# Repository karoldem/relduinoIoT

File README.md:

# relduinoIoT
KiCAD project of Arduinoish board with relay and ESP-01 on it.

Disclaimer - I hereby reject any responsibility for usage of this device. Seriously, guys, don't plug any random schematic form Internet to the grid without being trained electrician.

On board:
  ESP-01
  4 relays
  6 channel ADC
  2 PWM channels
  LEDS and microswitches
  
Not on a board:
  5V 1A power supply (I will use obsolete phone charger, that comes dime a dozen)

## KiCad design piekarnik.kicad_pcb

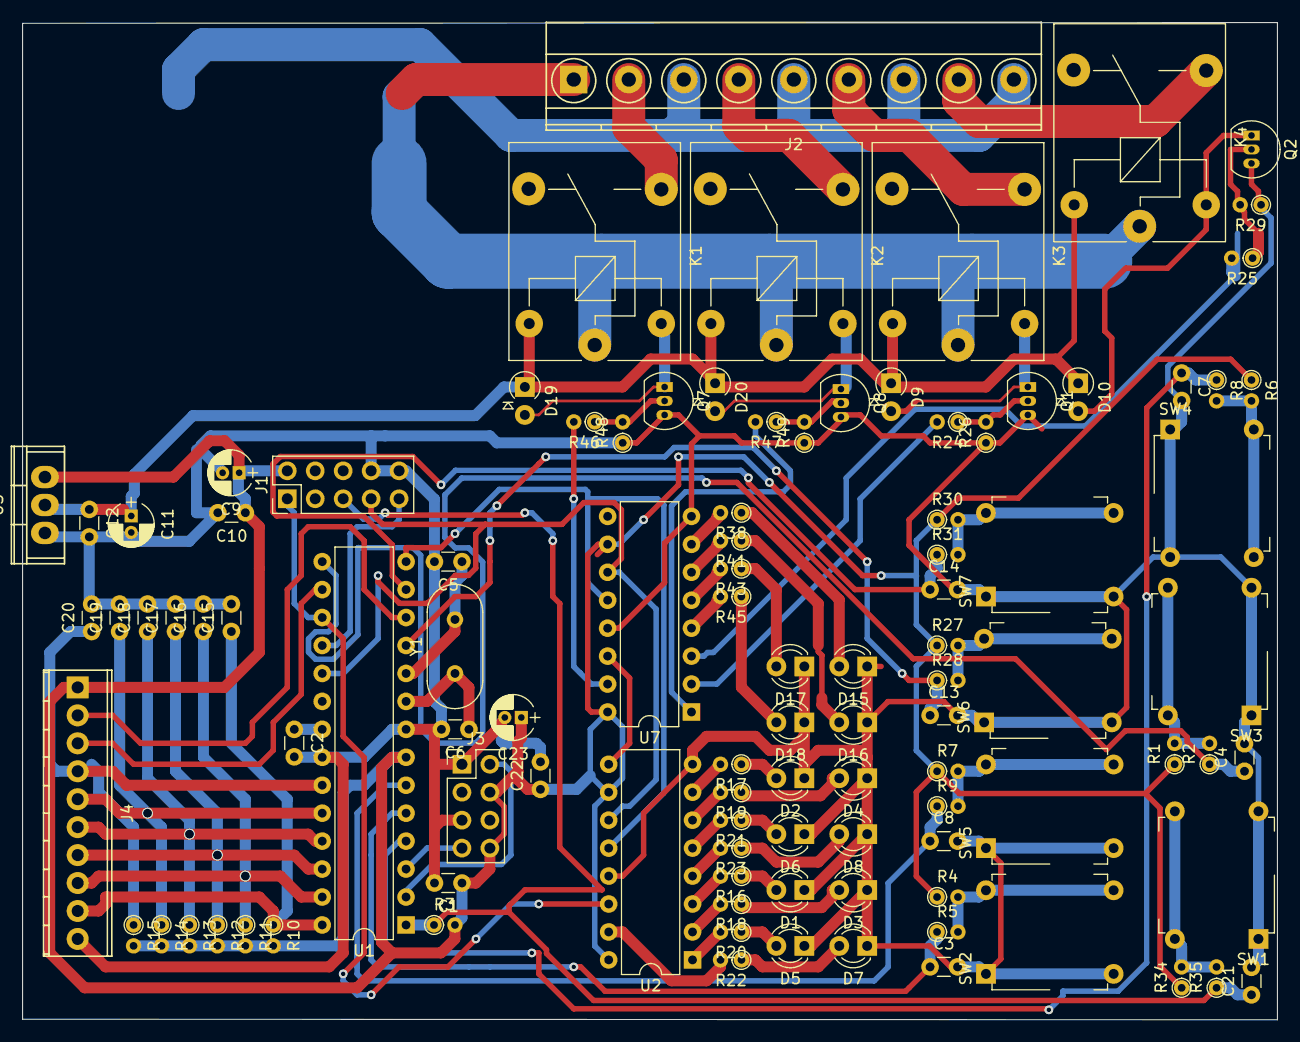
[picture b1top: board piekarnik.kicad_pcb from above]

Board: 2 copper layers, 114.1 x 90.6 mm, 104 parts (0 on the bottom side), 77 nets.

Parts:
C1, C2, C10, C12, C15, C16, C17, C18, C19, C20, C22: 100n; C_Disc_D3.0mm_W1.6mm_P2.50mm
C3, C4, C7, C8, C13, C14, C21: 10u; C_Disc_D3.0mm_W1.6mm_P2.50mm
C5, C6: 22p; C_Disc_D3.0mm_W1.6mm_P2.50mm
C9, C11, C23: 22u; CP_Radial_D4.0mm_P1.50mm
D1, D2, D3, D4, D5, D6, D7, D8, D15, D16, D17, D18: LED; LED_D3.0mm
D9, D10, D19, D20: D; D_A-405_P2.54mm_Vertical_AnodeUp
J1: Conn_02x05_Odd_Even; PinHeader_2x05_P2.54mm_Vertical
J2: Screw_Terminal_01x09; TerminalBlock_Phoenix_MKDS1.5-9pol
J3: Conn_02x04_Odd_Even; PinHeader_2x04_P2.54mm_Vertical
J4: Screw_Terminal_01x10; TerminalBlock_Phoenix_MPT-2.54mm_10pol
K1, K2, K3, K4: SANYOU_SRD_Form_C; Relay_SPDT_SANYOU_SRD_Series_Form_C
Q1, Q2, Q7, Q8: BC237; TO-92_Inline_Narrow_Oval
R1, R2, R3, R4, R5, R6, R7, R8, R9, R10, R11, R12, R13, R14, R15, R27, R28, R30, R31, R34, R35: 10k; R_Axial_DIN0204_L3.6mm_D1.6mm_P1.90mm_Vertical
R16, R17, R18, R19, R20, R21, R22, R23, R38, R41, R43, R45: 220; R_Axial_DIN0204_L3.6mm_D1.6mm_P1.90mm_Vertical
R24, R25, R46, R47: 1k; R_Axial_DIN0204_L3.6mm_D1.6mm_P1.90mm_Vertical
R26, R29, R48, R49: 15k; R_Axial_DIN0204_L3.6mm_D1.6mm_P1.90mm_Vertical
SW1, SW2, SW3, SW4, SW5, SW6, SW7: SW_MEC_5E; SW_MEC_5GTH9
U1: ATmega88-20PU; DIP-28_W7.62mm
U2, U7: 74HC595; DIP-16_W7.62mm
U3: LM1117-3.3; TO-220
Y1: Crystal; Crystal_HC18-U_Vertical

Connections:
+3V3: C1.1, C9.1, C10.1, C22.1, C23.1, J1.2, J3.4, J3.8, J4.1, R1.1, R3.2, R4.1, R6.1, R7.1, R10.2, R11.2, R12.2, R13.2, R14.2, R15.2, R27.1, R30.1, R34.1, U1.7, U2.10, U2.16, U3.3, U7.10, U7.16
+5V: C11.1, C12.1, D9.1, D10.1, D19.1, D20.1, K1.5, K2.5, K3.5, K4.5, U3.2
/Line: J2.1, K1.1, K2.1, K3.1, K4.1
/MISO: J1.9, U1.18
/MOSI: J1.1, U1.17, U2.14
/Neutral: J2.3, J2.5, J2.7, J2.9
/RST: C21.1, J1.5, R3.1, R35.1, U1.1
/RX: J3.2, U1.2
/SCK: J1.7, U1.19, U2.11, U7.11
/TX: J3.7, U1.3
/button1: C4.1, R2.1, U1.15
/button2: C7.1, R8.1, U1.4
/button3: C3.1, R5.1, U1.5
/button4: C8.1, R9.1, U1.6
/button5: C13.1, R28.1, U1.11
/button6: C14.1, R31.1, U1.13
/sw1: J2.2, K1.3
/sw2: J2.4, K2.3
/sw3: J2.6, K3.3
/sw4: J2.8, K4.3
/swin1: R46.2, U7.15
/swin2: R47.2, U7.1
/swin3: R24.2, U7.2
/swin4: R25.2, U7.3
/~SS~: U1.14, U2.12, U7.12
GND: C1.2, C2.2, C3.2, C4.2, C5.2, C6.2, C7.2, C8.2, C9.2, C10.2, C11.2, C12.2, C13.2, C14.2, C15.2, C16.2, C17.2, C18.2, C19.2, C20.2, C21.2, C22.2, C23.2, D1.1, D2.1, D3.1, D4.1, D5.1, D6.1, D7.1, D8.1, D15.1, D16.1, D17.1, D18.1, J1.8, J1.10, J3.1, J3.5, J4.10, Q1.3, Q2.3, Q7.3, Q8.3, R26.1, R29.1, R48.1, R49.1, SW1.1, SW1.2, SW2.1, SW2.2, SW3.1, SW3.2, SW4.1, SW4.2, SW5.1, SW5.2, SW6.1, SW6.2, SW7.1, SW7.2, U1.8, U1.22, U2.8, U2.13, U3.1, U7.8, U7.13
unnamed: C2.1, U1.21
unnamed: C5.1, U1.10, Y1.2
unnamed: C6.1, U1.9, Y1.1
unnamed: C15.1, J4.9, R10.1, U1.28
unnamed: C16.1, J4.8, R11.1, U1.27
unnamed: C17.1, J4.7, R12.1, U1.26
unnamed: C18.1, J4.6, R13.1, U1.25
unnamed: C19.1, J4.5, R14.1, U1.24
unnamed: C20.1, J4.4, R15.1, U1.23
unnamed: D1.2, R16.1
unnamed: D2.2, R17.1
unnamed: D3.2, R18.1
unnamed: D4.2, R19.1
unnamed: D5.2, R20.1
unnamed: D6.2, R21.1
unnamed: D7.2, R22.1
unnamed: D8.2, R23.1
unnamed: D9.2, K3.2, Q1.1
unnamed: D10.2, K4.2, Q2.1
unnamed: D15.2, R38.1
unnamed: D16.2, R41.1
unnamed: D17.2, R43.1
unnamed: D18.2, R45.1
unnamed: D19.2, K1.2, Q7.1
unnamed: D20.2, K2.2, Q8.1
unnamed: J4.2, U1.12
unnamed: J4.3, U1.16
unnamed: Q1.2, R24.1, R26.2
unnamed: Q2.2, R25.1, R29.2
unnamed: Q7.2, R46.1, R48.2
unnamed: Q8.2, R47.1, R49.2
unnamed: R1.2, R2.2, SW3.3, SW3.4
unnamed: R4.2, R5.2, SW2.3, SW2.4
unnamed: R6.2, R8.2, SW4.3, SW4.4
unnamed: R7.2, R9.2, SW5.3, SW5.4
unnamed: R16.2, U2.3
unnamed: R17.2, U2.7
unnamed: R18.2, U2.2
unnamed: R19.2, U2.6
unnamed: R20.2, U2.1
unnamed: R21.2, U2.5
unnamed: R22.2, U2.15
unnamed: R23.2, U2.4
unnamed: R27.2, R28.2, SW6.3, SW6.4
unnamed: R30.2, R31.2, SW7.3, SW7.4
unnamed: R34.2, R35.2, SW1.3, SW1.4
unnamed: R38.2, U7.7
unnamed: R41.2, U7.6
unnamed: R43.2, U7.5
unnamed: R45.2, U7.4
unnamed: U2.9, U7.14
